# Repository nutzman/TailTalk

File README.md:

# TailTalk

[![Crates.io][crates-badge]][crates-url] [![docs.rs][docs-badge]][docs-url]

[crates-badge]: https://img.shields.io/crates/v/tailtalk.svg
[crates-url]: https://crates.io/crates/tailtalk
[docs-badge]: https://img.shields.io/docsrs/tailtalk.svg
[docs-url]: https://docs.rs/tailtalk/latest/tailtalk/

TailTalk is designed as a "toolkit" for building fully userspace AppleTalk implementations on Linux, Mac OS and Windows
systems via EtherTalk or LocalTalk networks. It is built from scratch with zero dependencies on Netatalk or any kernel
drivers - All it needs is a raw socket and/or TashTalk compatible device (for LocalTalk) and patience for grumpy old computers.
It provides a complete AppleTalk stack, with multiple copies of it able to run on the same machine
at the same time.

I started this project to be able to copy files to/from my old Macs, print to LaserWriters and networked StyleWriters, and be able
to write modern async software to communicate with them. Currently TailTalk only works in a routerless setup - work is in progress
to make it gracefully join router present networks but it is not yet in the mainline code.

Each part of the stack is meant to be as "zero config" as possible, just like running on a Mac of the era. Just plug it in,
launch and things should just work without any fuss.

This project is very much a work in progress prototype, so expect bugs and missing features.

## TailTalk GUI

This is the current user facing program for use with TashTalk USB. It includes an AFP server which should work with just about
every Mac that shipped with a LocalTalk port. It also can import Stuff-It archives and floppy disk images and load them in to
the share path preserving the resource forks and make them available to remote clients.

It additionally supports sharing LocalTalk capable LaserWriters and StyleWriters to modern networks as AirPrint / IPP printers,
and sharing modern printers to classic Macs. The latest release can be found here:

[https://github.com/FeralFirmware/TailTalk/releases/latest](https://github.com/FeralFirmware/TailTalk/releases/latest)

## Features

Packet parsers and fully async APIs for almost all the major AppleTalk protocols.

- AppleTalk Address Resolution Protocol (AARP)
- Datagram Delivery Protocol (DDP)
- Name Binding Protocol (NBP)
- AppleTalk Transaction Protocol (ATP)
- Printer Access Protocol (PAP)
- AppleTalk Session Protocol (ASP)
- AppleTalk Filing Protocol (AFP)
- AppleTalk Data Stream Protocol

It additionally supports running with TashTalk for LocalTalk Macs.

The AARP/DDP underlay can run either in-process (the default) or in a shared
daemon, `tailtalkd`, which owns the interfaces and serves DDP sockets,
addressing, and routing rules to multiple clients over a protobuf protocol on
a Unix or UDP socket — usable from TailTalk (`TalkStack::builder().daemon_unix(..)`)
or plain C clients. See [docs/daemon-protocol.md](docs/daemon-protocol.md).

## Building

### Prerequisites

This project requires Rust 1.90 or above, which can be installed from [rustup.rs](https://rustup.rs). This should install
a matching compiler for your OS and CPU architecture by default.

This project uses [cargo-packager](github.com/crabnebula-dev/cargo-packager) for building AppImage for Linux, and App bundles
for macOS and installers for Windows. Install it with `cargo install cargo-packager`.

### Windows Only

Ensure you have the Windows MSVC prerequisites installed as specified in the [rustup book](https://rust-lang.github.io/rustup/installation/windows-msvc.html).

Windows requires the npcap SDK to be saved somewhere on your machine. It is available at [npcap.com](https://npcap.com/#download). Point a LIB environment variable to the folder where you unzipped the SDK, such as:
``` C:\npcap-sdk-1.13\Lib\x64```

### Running the build

Once the prerequisites are installed, run `cargo build --release` from the root of this repository to build everything, or for just the
TailTail GUI run `cargo build -p tailtalk-gui --release`.

After building the binaries should be located at `target/release/`.

Then run the following based on your OS:
```sh
# Linux
cargo packager --release -f appimage -p tailtalk-gui
# macOS
cargo packager --release -p tailtalk-gui
# Windows 
cargo packager --release -f nsis -p tailtalk-gui

```

The resulting bundle will be placed in dist/. 

## TashTalk USB

Quick start guide: [Setup.md](/Setup.md)

TashTalk USB uses a Silicon Labs CP210x USB-to-UART bridge (VID `10c4`, PID `ea60`). 

### Linux
The `cp210x` kernel module is likely installed already but by default the device node is only accessible by root. To grant your user
access without requiring root, create a udev rule:

```sh
echo 'SUBSYSTEM=="tty", ATTRS{idVendor}=="10c4", ATTRS{idProduct}=="ea60", TAG+="uaccess"' \
  | sudo tee /etc/udev/rules.d/99-tashtalk-usb.rules
sudo udevadm control --reload-rules && sudo udevadm trigger
```

After running these commands, unplug and re-plug the TashTalk USB device. It will appear as `/dev/ttyUSB0` (or
similar) and be accessible without root.

### Windows
Install the CP210x VCP Windows driver from 
[Silicon Labs](https://www.silabs.com/software-and-tools/usb-to-uart-bridge-vcp-drivers?tab=downloads).

Install npcap 1.88 from [npcap.com](https://npcap.com/#download)

### MacOS
macOS 11 and later includes support for the CP2102N USB chip out of the box. For 10.12 through 10.15 the driver from Silicon
Labs is required for the device to be recognised: https://www.silabs.com/software-and-tools/usb-to-uart-bridge-vcp-drivers?tab=downloads

## Existing Programs
There are 4 demo programs I have written to verify the functionality of this software as I have developed it:

- [aep-echo](/examples/aep-echo/) - A simple echo program that sends an echo request to a target address and prints the response time.
- [afp-server](/examples/afp-server) - An AFP 1.0, 1.1 and 2.0 compatible AFP server. Very much a work in progress but is capable of reading and writing files to classic Mac systems. Basic directory browsing and file operations are supported.
- [nbp-lookup](/examples/nbp-lookup) - Performs an NBP lookup based on the provided request string and returns the results
- [pap-print](/examples/pap-print) - Sends a PostScript file to a PAP printer. Aimed at LaserWriters, and have only tested on my own 4/600 PS.
- [tailtalkd](/tailtalk-daemon/) - The TailTalk underlay daemon. Owns the physical AppleTalk interfaces and serves DDP sockets, addressing, and routing to client applications over a Unix/UDP socket.
- [tailtalk-gui](/examples/tailtalk-gui/) - A simple GUI for sharing a folder as a volume over EtherTalk and/or LocalTalk (via TashTalk).

All of the examples run a complete copy of the stack using a raw socket (if EtherTalk is enabled) and thus need to be run as root,
 or the appropriate setcap applied to the compiled binary. If only using TashTalk then this is not required.

## Testing

Beyond unit tests I have found the best way to test this software is with real hardware. My current test setup consists of:

- Linux machine running TailTalk
- PowerBook G3 running Mac OS 9.2 via Ethernet
- LaserWriter 4/600 PS via AsanteTalk
- Color StyleWriter 2200 via EtherTalk adapter
- Macintosh SE/30 running System 7.1 via AsanteTalk
- Macintosh Classic running System 6.0.8 via AsanteTalk

### AsanteTalk

When the AsanteTalk is first powered on it "listens" for incoming packets on the Ethernet
side before choosing what EtherTalk phase to operate under. If it doesn't see any EtherTalk Phase 2 packets it will default to
Phase 1. TailTalk supports Phase 1 and this works just fine for LaserWriters, NBP and some basic operations but does
not work with AFP (The Mac will discover the AFP TailTalk server but our responses appear to be dropped).

## Contributing

I'd love to see this project grow into something that can be used to build more complete AppleTalk implementations. All contributions 
are welcome, but please open an issue first to discuss the changes you'd like to make. Additionally Pull Requests should mention what 
systems the change was verified against. This project has made me realise how quirky old systems are.

## License

This project is licensed under the GNU General Public License v3.0 - see the [LICENSE](LICENSE) file for details.

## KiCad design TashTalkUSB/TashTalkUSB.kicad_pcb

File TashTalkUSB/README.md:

## Overview

This device us a USB-ified version of [TashTalk by Tashtari](https://github.com/lampmerchant/tashtalk) using the original PIC12F1840 and a CP2102N USB-to-UART chip.

It uses the same firmware (v2.1.3 as of time of writing) from the original project, an an SN65HVD1473 transceiver from TI so it can be
used with a regular LocalTalk cable, or a dongle like PhoneNET. 

### Programming PIC

These boards use a [TagConnect cable](https://www.tag-connect.com/product/tc2030-pkt-nl-6-pin-no-legs-cable-for-microchip-pickit-3) for connecting to the board for programming. If using the PICkit to power the circuit during bringup ensure that the supply voltage is set to 3.3V - 5V will destroy the 
other chips on the board.

I use [Microchip's IPE](https://www.microchip.com/en-us/tools-resources/production/mplab-integrated-programming-environment) for bulk programming these
devices. No extra settings need to be changed beyond the supply voltage if powering it off the PICkit. Just burn the firmware on to the device
and it should be ready to go. 

### Programming CP2102N

The CP2102N should work out of the box, but does not have the LED alternate mode immediately enabled (so the little RX/TX LEDs light up). I use [cp210x-cfg](https://github.com/cr1tbit/cp210x-cfg) along with [tashtalk-setup.sh](/TashTalkUSB/tashtalk-setup.sh) to provision these. This script only works on Linux
today but could be adapted for other platforms if needed.

This little script enables the LED mode and sets the device name and manufacturer so it comes up with a friendly name in TailTalk. It is not strictly necessary to do this of course.

The script launches and will wait for the first TashTalk USB device to be plugged in. Once detected it will then set all the values and wait
for the next one to be plugged in. It is pretty helpful for mass programming these for a bulk order. 

### Verification

Once both the PIC and CP2102N have been programmed I typically test this by launching TailTalk, starting the server and verifying a vintage Mac can
connect and see files from it. TashTalk can auto reconnect to TashTalk so if bulk testing you can simply unplug the USB and DIN cable, swap to another
and then resume testing.

The tests pass if the remote Mac can successfully discover the server and query files from it, and the LEDs work on the board. 

### Manufacturing 

I use JLCPCB for making these boards and the schematics and board files are already prepared with LCSC part numbers for each component. I've tried to
choose their basic components as much as possible to keep costs down. If doing a large order panelisation is recommended as the individual boards are 
really small and a high cost per board is paid when not panelised.

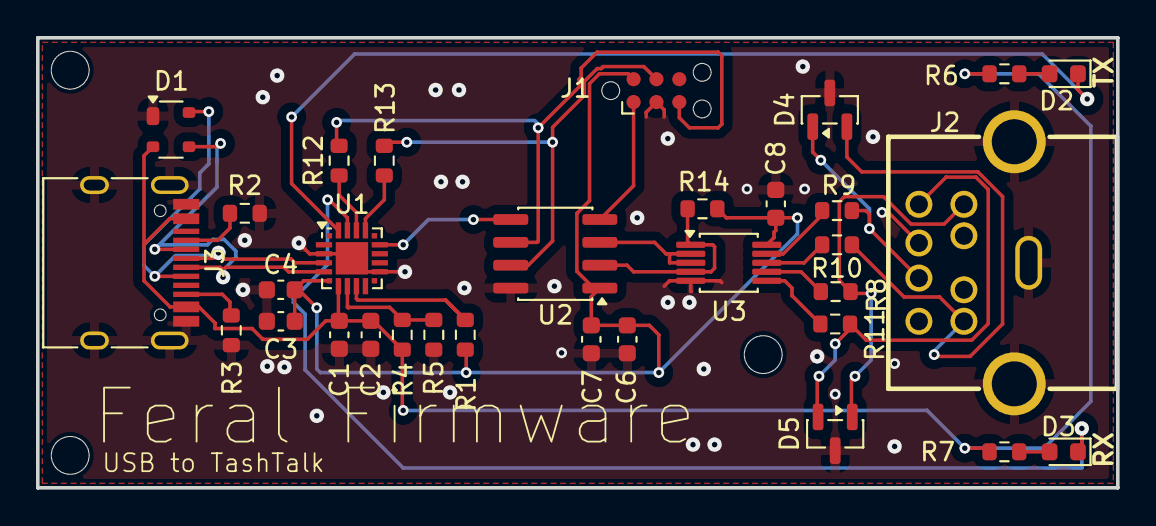
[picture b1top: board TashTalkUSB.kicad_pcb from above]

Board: 2 copper layers, 60.0 x 25.0 mm, 32 parts (0 on the bottom side), 29 nets.

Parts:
C1, C3, C6, C8: 0.1uF; C_0603_1608Metric
C2, C4, C7: 4.7uF; C_0603_1608Metric
D1: SP0503BAHT; SOT-143
D2: Blue; LED_0603_1608Metric
D3: Green; LED_0603_1608Metric
D4, D5: SM712_SOT23; SOT-23
J1: TC2030; Tag-Connect_TC2030-IDC-NL_2x03_P1.27mm_Vertical
J2: CONN-TH_DIN-802
J3: USB_C_Receptacle_USB2.0_14P; USB_C_Receptacle_HRO_TYPE-C-31-M-12
R1: 1K; R_0603_1608Metric
R2, R3: 5K1; R_0603_1608Metric
R4: 22K1; R_0603_1608Metric
R5: 47K5; R_0603_1608Metric
R6: 300; R_0603_1608Metric
R7: 240; R_0603_1608Metric
R8, R9, R10, R11: 10; R_0603_1608Metric
R12, R13: 100; R_0603_1608Metric
R14: 10K; R_0603_1608Metric
U1: CP2102N-Axx-xQFN20; SiliconLabs_QFN-20-1EP_3x3mm_P0.5mm_EP1.8x1.8mm
U2: PIC12F1840-xSN; SOIC-8_3.9x4.9mm_P1.27mm
U3: SN65HVD1473DGSR; MSOP-10_3x3mm_P0.5mm

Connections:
+3.3V: C3.1, C4.1, C6.1, C7.1, C8.1, J1.2, R1.1, R14.1, U1.6 (VDD), U2.1 (VDD), U3.10 (VCC)
+5V: C1.1, C2.1, D1.2 (K), J3.A4 (VBUS), J3.A9 (VBUS), J3.B4 (VBUS), J3.B9 (VBUS), R4.1, R6.1, R7.1, U1.7 (VREGIN)
A: D4.1 (A1), J2.7, R9.2
B: D4.2 (A2), J2.4, R10.2
CC1: J3.A5 (CC1), R2.1
CC2: J3.B5 (CC2), R3.1
D+: D1.4 (K), J3.A6 (D+), J3.B6 (D+), U1.4 (D+)
D-: D1.3 (K), J3.A7 (D-), J3.B7 (D-), U1.5 (D-)
DE: U2.3 (RA4), U3.2 (RE), U3.3 (DE)
DIN3: D5.1 (A1), J2.3, R8.2
DIN6: D5.2 (A2), J2.5, R11.2
GND: C1.2, C2.2, C3.2, C4.2, C6.2, C7.2, C8.2, D1.1 (A), D4.3 (common), D5.3 (common), J1.3, J2.8, J2.9, J2.10, J2.11, J3.A1 (GND), J3.A12 (GND), J3.B1 (GND), J3.B12 (GND), J3.S1 (SHIELD), R2.2, R3.2, R5.2, U1.3 (GND), U1.12 (GND), U1.21 (GND), U2.8 (VSS), U3.5 (GND)
ICSPCLK: J1.5, R12.2, U2.6 (RA1)
ICSPDAT: J1.4, R13.2, U2.7 (RA0)
LocalTalk: R14.2, U2.2 (RA5), U3.1 (R), U3.4 (D)
MCLR: J1.1, U2.4 (RA3)
unnamed: D2.2 (A), R6.2
unnamed: D2.1 (K), U1.20 (~TXT/GPIO.2)
unnamed: D3.2 (A), R7.2
unnamed: D3.1 (K), U1.19 (~RXT/GPIO.3)
unnamed: R13.1, U1.17 (RXD)
unnamed: R12.1, U1.18 (TXD)
unnamed: R4.2, R5.1, U1.8 (VBUS)
unnamed: U1.15 (~CTS), U2.5 (RA2)
unnamed: R1.2, U1.9 (~RST)
unnamed: R9.1, U3.9 (A)
unnamed: R10.1, U3.8 (B)
unnamed: R11.1, U3.6 (Y)
unnamed: R8.1, U3.7 (Z)

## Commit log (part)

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2026-05-03 TashTalkUSB: Final rev 2
2026-05-03 GUI: Only display cu device on macOS
2026-05-08 DDP: Truncate to header size
    Fixes a fault on TashTalk runs where we would end up passing through
    the CRC bytes in to the payload. Since the DDP layer and above did
    not truncate the payload size to the header indicated size, our
    ATP layer could accidentally include this, and eventually corrupt
    AFP Classic Mac -> TailTalk transfers.
2026-05-09 Add config for packaging in to macOS app and appImage for Linux
2026-05-09 Bump rand from 0.8.5 to 0.9.3
    Bumps [rand](https://github.com/rust-random/rand) from 0.8.5 to 0.9.3.
    - [Release notes](https://github.com/rust-random/rand/releases)
    - [Changelog](https://github.com/rust-random/rand/blob/0.9.3/CHANGELOG.md)
    - [Commits](https://github.com/rust-random/rand/compare/0.8.5...0.9.3)
    ---
    updated-dependencies:
2026-05-10 Logs: Log to ~/Library/Logs on macOS for GUI, fix clippy
2026-05-10 Remove remaining GUI files from examples dir
2026-05-11 CI: Add first pass at build + release upload
2026-05-11 Prepare release 0.1.1
2026-05-12 fix: Stack restarts, add permission error handling, AFP lazy load, and fix shutdown
    Based on feedback this fixes a handful of issues:
    AFP - Switch to lazy loading subdirectories. Previously we would walk _everything_
    at volume mount to build a file database. For large dirs this could take a painfully
    long time unnecessarily. With this change we only load the root directory of the
    share at volume mount time, and then lazily load subdirs as requested by end users.
    TashTalk usage: Add a quick note on the dialout group users should be in to be
2026-05-12 Prepare release 0.1.2
2026-05-12 GUI: Store last settings and reload on startup
    Automatically saves the last chosen server name, volume path+name,
    and USB device (and optionally ethernet), and then reloads it if present
    at startup.
2026-05-13 ATP: Pass max response size through stack
    ATP (and by extension ASP) did not provide command receivers
    with a way of knowing what the maximum response size was. This could
    lead endpoints to try and send more data, and ATP/ASP would then
    semi-silently clip the data, causing potential corruption.
    With this we know pass through the maximum response size a client
    may actually send. Additional work should probably be done here to
2026-05-13 Prepare release 0.1.3
2026-05-13 Prepare Tashtalk release 0.2.1
2026-05-13 Doc: Add udev rule command for TashTalk USB
    Updates the project README to change the instructions for TashTalk
    USB from the dialout group to an easier udev rule. This should
    ensure the logged in user can access it without root access or specific
    groups.
2026-05-14 GUI+AFP: Auto-refresh serial devices, disable start button til ready, implement AFP 1.x cmds
    Updates the GUI so we refresh the list of available serial devices every 1.5 seconds
    on a Slint background timer. Additionally makes it so the Start button can only
    be pressed if all the available options are valid.
    Additionally adds the decomposed FPGetFileDirParms File and Dir equivalents for AFP 1.x
    clients that are running System 6 and earlier.
2026-05-15 GUI: Add Pcap option for debugging
    Adds a new Pcap check box that can capture LocalTalk and/or EtherTalk
    packets that our stack is receiving and sending, which is rather handy
    for debugging.
    Additionally adds ATP retransmits to resend once every 2 seconds if a client
    fails to respond to a server initiated command.
    Lastly starts adding the first pass at App signing and notarisation for
2026-05-17 AFP+GUI: Add StuffIt import option, use NTFS ADS on Windows
    To make it easier to copy applications directly to Macs without requiring
    them to already have StuffIt installed, I thought it would be handy to
    have the option to expand a sit archive with the GUI and pre-load it in to
    the users chosen volume dir. With this we load the data and resource forks
    to the expected paths so a connected Mac can see the archive contents as if
    it was extracted locally. This is still a bit experimental but hopefully
2026-05-18 Prepare release 0.3.0
2026-05-21 Prepare release 0.3.1
2026-05-24 AFP: Use pure-magic crate for determining file types
    Swaps from the primary mechanism being extensions to determine file types
    to pure-magic, which will try and see what a file is versus just blindly
    trusting the extension like Windows. The fallbacks are still present
    if pure-magic cannot recognise any matches.
    This should allow things like plain text files without an extension to
    now automatically open in SimpleText.
2026-05-24 Prepare release 0.4.0
2026-05-24 GUI: Update layout
    Based on recommendations from Iantm from 68KMLA this commit tweaks
    our GUI's layout to have categorised sections. Additionally makes it
    so our pcap button enables and disables the file browser versus
    hiding and showing it.
2026-05-25 resolve_resource_fork_path(): use tokio for async I/O, and return resource fork length
2026-05-26 AFP+PAP: Use async metadata method, make PAP printable via stream
    Swaps our last std::fs call to tokio::fs so we are not doing blocking
    ops on the Tokio thread. Additionally adds a new PAP print method for
    streaming data to the remote side, versus requiring the entire buffer
    to be passed in at once.
2026-05-26 Prepare release 0.4.1 (GUI) and 0.2.3 (tashtalk)
2026-05-27 GUI: Add "Import HFS disk image" button
    In the same vein as the Stuff-It import added, this commit
    adds the option to import a raw HFS disk image, or a Disk Copy 4.2
    image. The image will then be parsed and all files and folders
    (including data+resource forks, icons and desktop entries) will be
    copied in to a matching folder name in the selected share path.
    To support this I have put together a rather simple little HFS read only
2026-05-28 Prepare release 0.4.2
2026-05-28 Mac: Use native resource forks by default
    Swaps macOS clients for our AFP server to using native resource
    forks versus sidecar files. There's no real need to use sidecars
    on an OS that natively supports them. For users upgrading from
    previous versions we will still fallback to loading from sidecars.
2026-05-30 AFP: Store comments by file path, not ID
    We do not persist file IDs across runs and instead lazily generate them.
    This means that comments added to one file ID might correspond to a different
    file on the next run. This swaps our backend storage to use the file path
    instead.
2026-05-30 AFP: Share sled Db across sessions
    Makes our Sled DB handle be shared across AFP sessions, rather than
    having each session attempt to create their own. This should get us
    closer toward having true multiple AFP session support (in fact right
    now it _should_ work, but a reader and writer to the same thing at the
    same time will cause issues).
2026-05-31 GUI: Per-character OSType input; TalkStack: add service helpers; AFP: expand type/creator inference; LocalTalk: handle framing errors in codec
    The Finder info type/creator editor now uses four individual single-character
    boxes that auto-advance focus, matching how OSType codes are entered on a real
    Mac. TalkStack gains convenience methods for AFP, ASP, ADSP, and PAP so
    callers no longer need to import internal types and wire up handles directly.
    The MIME -> type/creator table gains mappings for JPEG, PNG, PICT, MacBinary,
    DFont, BinHex 1.0/2.0, AppleWorks 3, DC42 floppies, and MPW π tools, plus a
2026-06-01 Prepare release 0.4.4
2026-06-02 AFP: Add name mangling support
    Coming from a report from Iesca on 68KMLA it was found that file names
    exceeding the AFP limit could be sent to clients and appeared to work
    OK, but would cause silent memory corruption on the classic Mac. It
    would then cause rather odd failures (In their case, the IIfx would freeze
    when trying to copy a file. On my 512K it could copy OK, but doing a Get Info
    on any folder containing along file name would cause an address error).
2026-06-03 ci: Add Windows builds
    Enables builds, tests and releases for Windows given that TailTalk (and
    by extension the GUI) work just fine on the platform after testing by
    a 68KMLA user. Thank you @nutzman!
    Tested-by: Josh Nutzman <josh@tradewinddatascience.com>
2026-06-05 Refactor to fix bugs with windows & pcap
2026-06-06 EtherTalk: Fix broadcast addressing for Phase 2 and NBP
    We were using FF:FF:FF:FF:FF:FF for all AppleTalk broadcast traffic
    regardless of phase. EtherTalk Phase 2 requires 09:00:07:FF:FF:FF for
    both AARP and DDP broadcasts.
    Addressing::spawn now takes an explicit phase, used to select the
    correct broadcast MAC for AARP probes and requests. try_lookup now
    resolves node 255 before checking network 0, so {0, 255} resolves
2026-06-06 ci: Add missing build phase for Windows releases
2026-06-06 Add simple progress box for HFS and StuffIt import
    Previously the import button would silently spawn a background task
    to import the data from the archive/image but for large ones it was
    not obvious it was working on it. Now a simple little box is displayed
    showing where it is at file wise to give feedback.
2026-06-07 Prepare release 0.5.1
2026-06-11 LocalTalk: Add option for fixed node address
    Adds a new builder opt for forcing a specific LocalTalk address
    when bringing up the stack.
2026-06-13 GUI: Swap to stuffit-rs fork (#23)
    Swaps to my stuffit-rs fork as it has a bugfix that the
    maintainer has yet to merge in upstream. Hopefully will only be
    temporary.
2026-06-14 TailTalk: Gate Pcap usage behind ethertalk flag (#25)
    Refactors our code base so only if the "ethertalk" feature flag is set
    do we actually pull in the pcap crate. This makes it so our packages
    published on GitHub which has this feature disabled does not actually
    require libpcap to be bundled (for macOS / Linux) or installed (for Windows).
    Additionally bumps our deps to the latest versions and some minor changes
    associated with the crate bumps.
2026-06-14 TashTalkUSB: Add programming/provisioning doc
2026-06-19 Fix protocol correctness bugs in NBP, DDP, ATP, and ASP (#27)
    NBP's fully_qualified() was rejecting zone "*", which is the standard
    AppleTalk registration convention for "my current zone" (resolved by the
    router). The check now only validates object and type for wildcard
    characters. The associated error message for a misplaced ':' was also
    backwards — it said "before @" when the condition fires when ':' is
    found after '@'.
2026-06-20 GUI: Add binhex import option, consolidate import methods (#28)
    Pulls in binhex-rs so we can import binhex'd files just like Netatalk.
    As part of this we also consolidate all the import buttons in to a single
    one that offers changing the archive type in the file picker.
2026-06-25 Stack: Add route table for multi-segment AppleTalk networking (#30)
    Introduces a RouteTable that maps DDP cable ranges to next-hop routers
    (RTMP) and zone names to cable ranges (ZIP), wired into both DDP outbound
    dispatch and NBP LkUp handling. This is the groundwork needed to operate
    on networks with a router or bridge present, such as a LocalTalk-to-
    Ethernet bridge like a Farallon EtherWave or AsanteTalk.
    With no routes programmed behaviour is identical to before. Routes are
2026-06-25 Prepare release 0.7.0
2026-06-28 GUI+AFP: Use shellexpand for ~ expansion, return volume errors to user (#31)
    Imports the shellexpand crate so that way manually entered paths will
    be able to use ~/ as part of the pathname. Previously we would end up
    resolving this to $CWD/~/ which when used with the macOS app version
    would give a confusing error.
    Additionally this error was only visible in the logs - when a Mac would
    try and connect we'd return a server unavailable error message and it
